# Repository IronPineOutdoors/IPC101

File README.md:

# Iron Pine Outdoors IPC-101

IPC-101 is a prototype operator-control-panel PCB for IPC-100. Revision P0 implements seven ordinary controls through a TCA8418 keypad scanner on IPC-100's protected 3.3 V J10 I2C expansion branch, physically carries the Hosyond 2.42-inch SSD1309 prototype display connected by a dedicated five-wire harness to IPC-100 J6, and carries the normally-closed STOP contact only on a separate J8A harness.

## Release state

**Rev C prototype fabrication package corrected for solder mask.** Use [IPC101_RevC_MaskFix_Gerbers.zip](hardware/fabrication/IPC101_RevC/IPC101_RevC_MaskFix_Gerbers.zip) and the existing Rev C BOM/CPL. The superseded package omitted through-hole solder-mask openings; the replacement contains verified top and bottom openings. Full KiCad DRC passes with 0 violations and 0 unconnected pads. See [order notes](hardware/fabrication/IPC101_RevC/ORDER_NOTES.md) and [verification results](hardware/fabrication/IPC101_RevC/MASK_FIX_VALIDATION.md).

The Rev C board is 150 x 100 mm. Physical control/display/faceplate fit remains a prototype acceptance check; the bare PCB has no ingress rating.

## Architecture

- START, PULL: Omron B3F-4055 12 mm through-hole tactile switches.
- Navigation: Adafruit 504 five-way through-hole switch (LEFT/RIGHT/UP/DOWN/SELECT).
- STOP: Omron A22NE-M-PD01-N, normally-closed contact, panel mounted; its two wires remain isolated from PCB logic and pass through dedicated connector J3.
- Key scanner: TI TCA8418RTWR at fixed I2C address `0x34`, polled by IPC-100; 7x1 matrix.
- Display: Hosyond 2.42-inch 128x64 I2C SSD1309 module (Amazon ASIN B0G2RFLG1L), mounted to the faceplate using the corrected Crosswind geometry and connected through IPC-101 J2/J4 to IPC-100 J6.
- IPC-100 ordinary-control link: J10, JST GH 4-pin, 3.3 V / 100 mA / 100 kHz I2C.

## Next-board planning

[IPC-101 Rev 2 planning notes](docs/requirements/IPC101_REV2_PLANNING.md) capture BME280 support, corrected 504 pin alignment, rear input-connector evaluation, direct PCB-mounted OLED, and complete silkscreen/board identification. This is a requirements backlog; current fabrication files are unchanged.

## Repository map

- `docs/` — controlled requirements, decisions, interfaces, mechanics, and test plan.
- `hardware/kicad/` — KiCad project, schematic, routed PCB, and project-local footprints.
- `hardware/bom/` — prototype BOM.
- `hardware/fabrication/` — release notes and generation instructions; verified Gerbers, drills, and assembly outputs are included.
- `mechanical/` — panel coordinate and cutout data.
- `manufacturing/` — assembly and inspection notes.

## Next action

Prepare for the incoming boards with the [Rev C arrival and first-power checklist](docs/testing/IPC101_REVC_ARRIVAL_CHECKLIST.md). It covers the actual order comparison, hand-installed parts, Rev D/Rev H mechanical fit, TPU coupons, harness verification, staged power-up, and result recording. Receipt and acceptance of the replacement manufacturing file must be confirmed against the order; the local package alone does not establish what was fabricated.

Upload the replacement Gerber ZIP to the held JLCPCB order and confirm both solder-mask layers in its viewer. Review assembly orientation before approving production, then fit-test and electrically validate the first prototype before connecting motion hardware.

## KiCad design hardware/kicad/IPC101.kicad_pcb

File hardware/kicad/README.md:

# IPC-101 Rev C KiCad Source

This directory contains the fabrication-oriented Rev C operator-control board for the Crosswind control-panel replacement.

## Rev C layout

- Board outline: 150 x 100 mm, matching the Rev C faceplate.
- OLED: left-side 2.42-inch Hosyond/SSD1309 mechanical pattern. The display mounts to the faceplate and plugs into IPC-101 J2; J4 carries the same isolated five-wire branch to IPC-100 J6 (`OLED_VCC`, `GND`, `SDA`, `SCL`, `RESET`).
- Navigation: Adafruit 504 five-way switch at the right side of the display row.
- Lower controls: ARM at left and PULL at right.
- Indicator: PCB-mounted 5 mm common-anode RGB LED centered between the lower controls and display row.
- Power-switch region: mechanically reserved only; no cutout or footprint is committed until the rated switch is selected.

The IPC-101 board connects to IPC-100 through J1 for keypad `+3V3`, `GND`, `SDA`, and `SCL`, through J4 for the dedicated OLED branch, and through J3 for isolated STOP. J2 is the local OLED harness output. The J2/J4 copper pass-through does not join the J1 keypad branch.

## Electrical implementation

- U1: TCA8418 keypad/GPIO controller in TI RTW-24 QFN.
- SW1: ARM; SW2: PULL; SW3: LEFT/RIGHT/UP/DOWN/SELECT.
- D1: 5 mm common-anode RGB LED.
- R2/R3/R4: 1 kOhm current-limiting resistors.
- RGB GPIO assignment: COL6/pad 15 red, COL7/pad 16 green, COL8/pad 17 blue.
- Two copper layers with 0.20 mm signal tracks, 0.15 mm clearance, and 0.50/0.30 mm vias.
- F.Cu `+3V3` plane and B.Cu ground plane with explicit island stitching.

`generate_rev_c_pcb.py` reproducibly rebuilds the placed and routed geometry from the embedded footprints. Run it with KiCad's bundled Python, then refill zones and rerun DRC if any placement or routing is edited interactively.

## Validation

- `IPC101_DRC.rpt`: full KiCad DRC, 0 violations and 0 unconnected items.
- `IPC101_ERC.rpt`: KiCad error-level ERC, 0 violations.
- `IPC101_RevC_3D.png`: top-side KiCad render for placement review.
- `IPC101_RevC.net.xml`: exported schematic netlist for parity/review tooling.

Before ordering a production quantity, print the Rev C faceplate and both caps, assemble one PCB, verify the Adafruit 504 physical pin orientation, and continuity-check both OLED harnesses against the received module and the documented J2/J4 pinouts.

## Solder-mask correction (2026-09-07)

The 29 PTH component pads now explicitly include both F.Mask and B.Mask. Copper routing and drill geometry are unchanged. `generate_rev_c_pcb.py` restores these layers for cloned as well as newly created PTH pads. Use the replacement `IPC101_RevC_MaskFix_Gerbers.zip`; the earlier package had an empty bottom mask and omitted top openings for the PTH pads. The fabrication export script audits source pad layers and every solderable pad centre in the archived mask files.

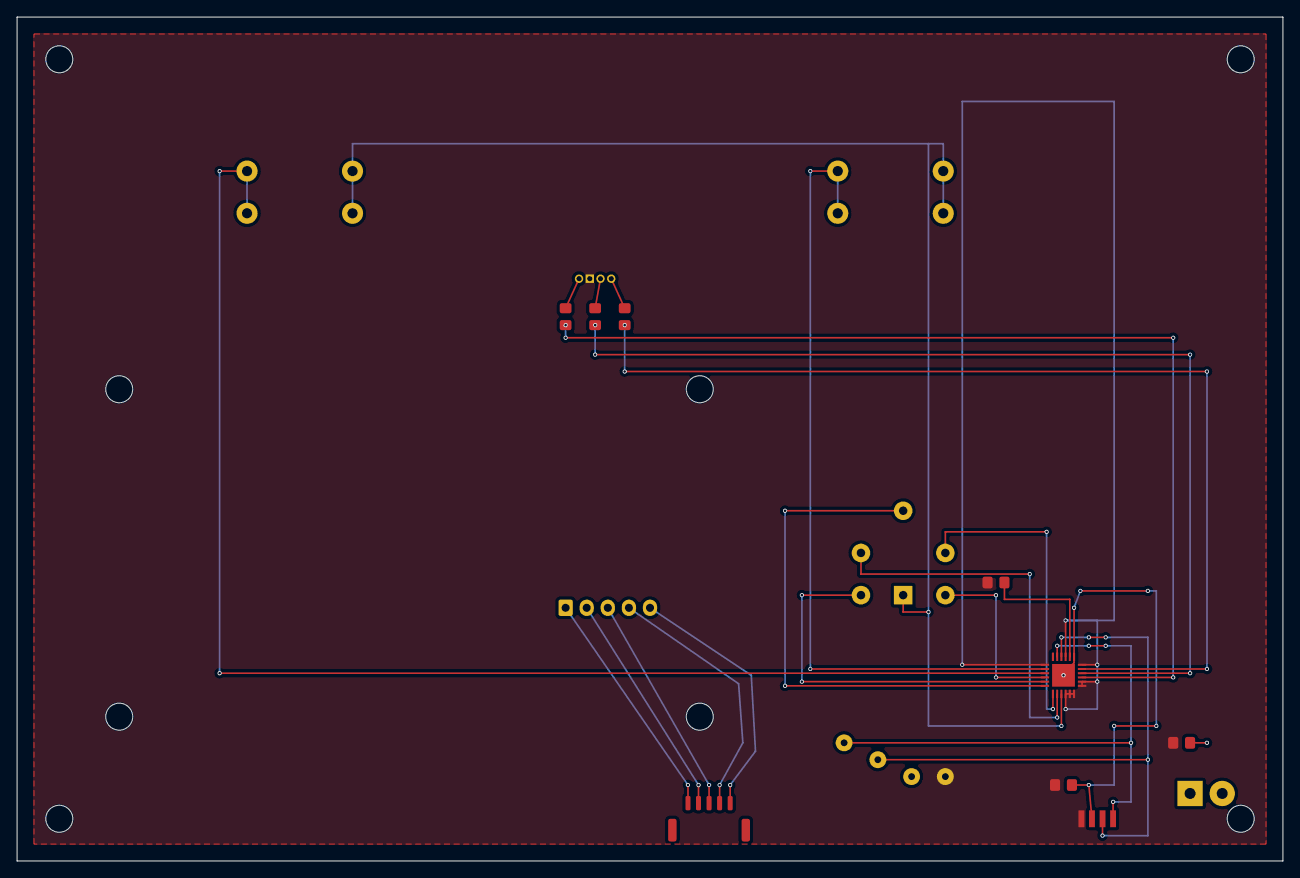
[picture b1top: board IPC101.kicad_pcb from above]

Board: 2 copper layers, 150.0 x 100.0 mm, 24 parts (0 on the bottom side), 24 nets.

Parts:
C1: 100nF
C2: 4.7uF
D1: 5MM RGB COMMON ANODE
DS1: HOSYOND 2.42in SSD1309 - 5 WIRE J6 HARNESS
H1, H2, H3, H4: (no value)
J1: IPC-100 J10
J2: OLED HARNESS OUTPUT
J3: IPC-100 J8A STOP
J4: IPC-100 J6 OLED INPUT
R1: 10k RESET
R2: 1k RED
R3: 1k GREEN
R4: 1k BLUE
SW1: ARM B3F-4055
SW2: PULL B3F-4055
SW3: ADAFRUIT 504 - VERIFY PIN MAP
TP1: +3V3
TP2: GND
TP3: SDA
TP4: SCL
U1: TCA8418RTWR

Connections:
/+3V3: C1.1, C2.1, D1.2, J1.1, R1.1, TP1.1 (1_1), U1.1 (ROW7), U1.10 (COL1), U1.11 (COL2), U1.12 (COL3), U1.13 (COL4), U1.14 (COL5), U1.18 (COL9), U1.21 (VCC)
/C0: SW1.2, SW2.2, SW3.1 (COMMON), U1.9 (COL0)
/GND: C1.2, C2.2, J1.2, TP2.1 (1_1), U1.19 (GND), U1.25 (EP)
/OLED_GND: J2.2, J4.2
/OLED_RESET: J2.5, J4.5
/OLED_SCL: J2.4, J4.4
/OLED_SDA: J2.3, J4.3
/OLED_VCC: J2.1, J4.1
/R0_LEFT: SW3.2 (LEFT), U1.8 (ROW0)
/R1_RIGHT: SW3.3 (RIGHT), U1.7 (ROW1)
/R2_UP: SW3.4 (UP), U1.6 (ROW2)
/R3_DOWN: SW3.5 (DOWN), U1.5 (ROW3)
/R4_SELECT: SW3.6 (SELECT), U1.4 (ROW4)
/R5_ARM: SW1.1, U1.3 (ROW5)
/R6_PULL: SW2.1, U1.2 (ROW6)
/RESET: R1.2, U1.20 (~RESET)
/RGB_B_GPIO: R4.1, U1.17 (COL8)
/RGB_B_K: D1.4, R4.2
/RGB_G_GPIO: R3.1, U1.16 (COL7)
/RGB_G_K: D1.3, R3.2
/RGB_R_GPIO: R2.1, U1.15 (COL6)
/RGB_R_K: D1.1, R2.2
/SCL: J1.4, TP4.1 (1_1), U1.23 (SCL)
/SDA: J1.3, TP3.1 (1_1), U1.22 (SDA)

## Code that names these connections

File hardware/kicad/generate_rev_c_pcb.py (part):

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
    # RGB GPIO channels use separated B.Cu levels before arriving at the SMD resistors.
    for name, pin_no, exit_x, level_y, resistor in (
        ("/RGB_R_GPIO", "15", 137.0, 38.0, "R2"),
        ("/RGB_G_GPIO", "16", 139.0, 40.0, "R3"),
        ("/RGB_B_GPIO", "17", 141.0, 42.0, "R4"),
    ):
        ni = net(board, name)
        source = pxy("U1", pin_no)
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            if len(pads) > 1 and name not in ("/GND", "/+3V3")]
    priority = {name: rank for rank, name in enumerate((
        "/SCL", "/SDA", "/RESET", "/INT_TEST",
        "/RGB_R_GPIO", "/RGB_G_GPIO", "/RGB_B_GPIO",
        "/RGB_R_K", "/RGB_G_K", "/RGB_B_K",
        "/R6_PULL", "/R5_ARM", "/R4_SELECT", "/R3_DOWN",
        "/R2_UP", "/R1_RIGHT", "/R0_LEFT", "/C0", "/GND", "/+3V3",
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
    u1 = existing["U1"]
    pad(u1, "3").SetNet(arm_net)
    rgb_gpio = ("/RGB_R_GPIO", "/RGB_G_GPIO", "/RGB_B_GPIO")
    for number, name in zip(("15", "16", "17"), rgb_gpio):
        pad(u1, number).SetNet(net(board, name))

    source_resistor = existing["R1"]
    resistors = (
        clone_resistor(board, source_resistor, "R2", "1k RED", 65.0, 35.5, "/RGB_R_GPIO", "/RGB_R_K"),
        clone_resistor(board, source_resistor, "R3", "1k GREEN", 68.5, 35.5, "/RGB_G_GPIO", "/RGB_G_K"),
        clone_resistor(board, source_resistor, "R4", "1k BLUE", 72.0, 35.5, "/RGB_B_GPIO", "/RGB_B_K"),
    )
    led = add_rgb_led(board)
    oled_nets = {
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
